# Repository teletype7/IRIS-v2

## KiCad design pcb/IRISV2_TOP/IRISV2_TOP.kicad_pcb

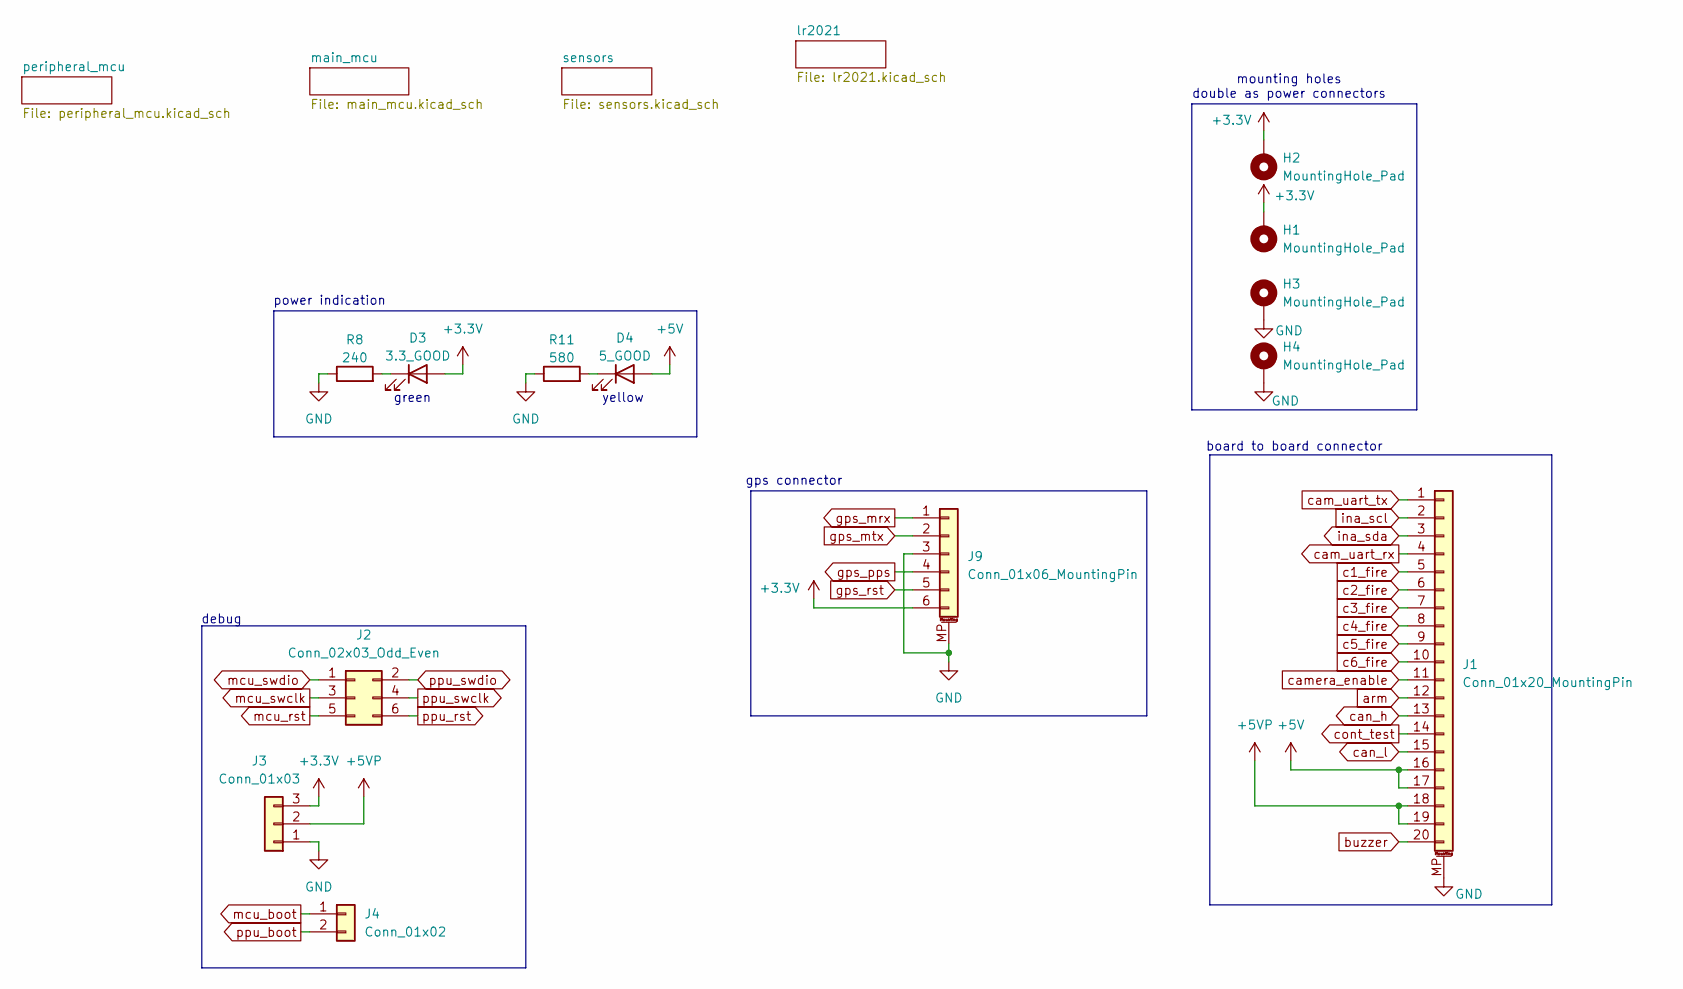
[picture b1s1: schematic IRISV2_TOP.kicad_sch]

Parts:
D3: 3.3_GOOD; LED_0805_2012Metric
D4: 5_GOOD; LED_0805_2012Metric
H1, H2, H3, H4: MountingHole_Pad; MountingHole_3.2mm_M3_ISO7380_Pad_TopBottom
J1: Conn_01x20_MountingPin; FFC3B07-20-T
J2: Conn_02x03_Odd_Even; PinHeader_2x03_P2.54mm_Vertical
J3: Conn_01x03; PinHeader_1x03_P2.54mm_Vertical
J4: Conn_01x02; PinHeader_1x02_P2.54mm_Vertical
J9: Conn_01x06_MountingPin; JST_PH_S6B-PH-SM4-TB_1x06-1MP_P2.00mm_Horizontal
R8: 240; R_0603_1608Metric
R11: 580; R_0603_1608Metric

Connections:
+3.3V: D3.2 (A), H1.1, H2.1, J3.3, J9.6; also elsewhere on the board
+5V: D4.2 (A), J1.16, J1.17; also elsewhere on the board
+5VP: J1.18, J1.19, J3.2
GND: H3.1, H4.1, J1.MP (MountPin), J3.1, J9.3, J9.MP (MountPin), R8.1, R11.1; also elsewhere on the board
unnamed: D3.1 (K), R8.2
unnamed: D4.1 (K), R11.2
arm: J1.12; also elsewhere on the board
buzzer: J1.20; also elsewhere on the board
c1_fire: J1.5; also elsewhere on the board
c2_fire: J1.6; also elsewhere on the board
c3_fire: J1.7; also elsewhere on the board
c4_fire: J1.8; also elsewhere on the board
c5_fire: J1.9; also elsewhere on the board
c6_fire: J1.10; also elsewhere on the board
cam_uart_rx: J1.4; also elsewhere on the board
cam_uart_tx: J1.1; also elsewhere on the board
camera_enable: J1.11; also elsewhere on the board
can_h: J1.13; also elsewhere on the board
can_l: J1.15; also elsewhere on the board
cont_test: J1.14; also elsewhere on the board
gps_mrx: J9.1; also elsewhere on the board
gps_mtx: J9.2; also elsewhere on the board
gps_pps: J9.4
gps_rst: J9.5
ina_scl: J1.2; also elsewhere on the board
ina_sda: J1.3; also elsewhere on the board
mcu_boot: J4.1; also elsewhere on the board
mcu_rst: J2.5; also elsewhere on the board
mcu_swclk: J2.3; also elsewhere on the board
mcu_swdio: J2.1; also elsewhere on the board
ppu_boot: J4.2; also elsewhere on the board
ppu_rst: J2.6; also elsewhere on the board
ppu_swclk: J2.4; also elsewhere on the board
ppu_swdio: J2.2; also elsewhere on the board

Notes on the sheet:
gps connector
debug
board to board connector
power indication
yellow
mounting holes double as power connectors
green

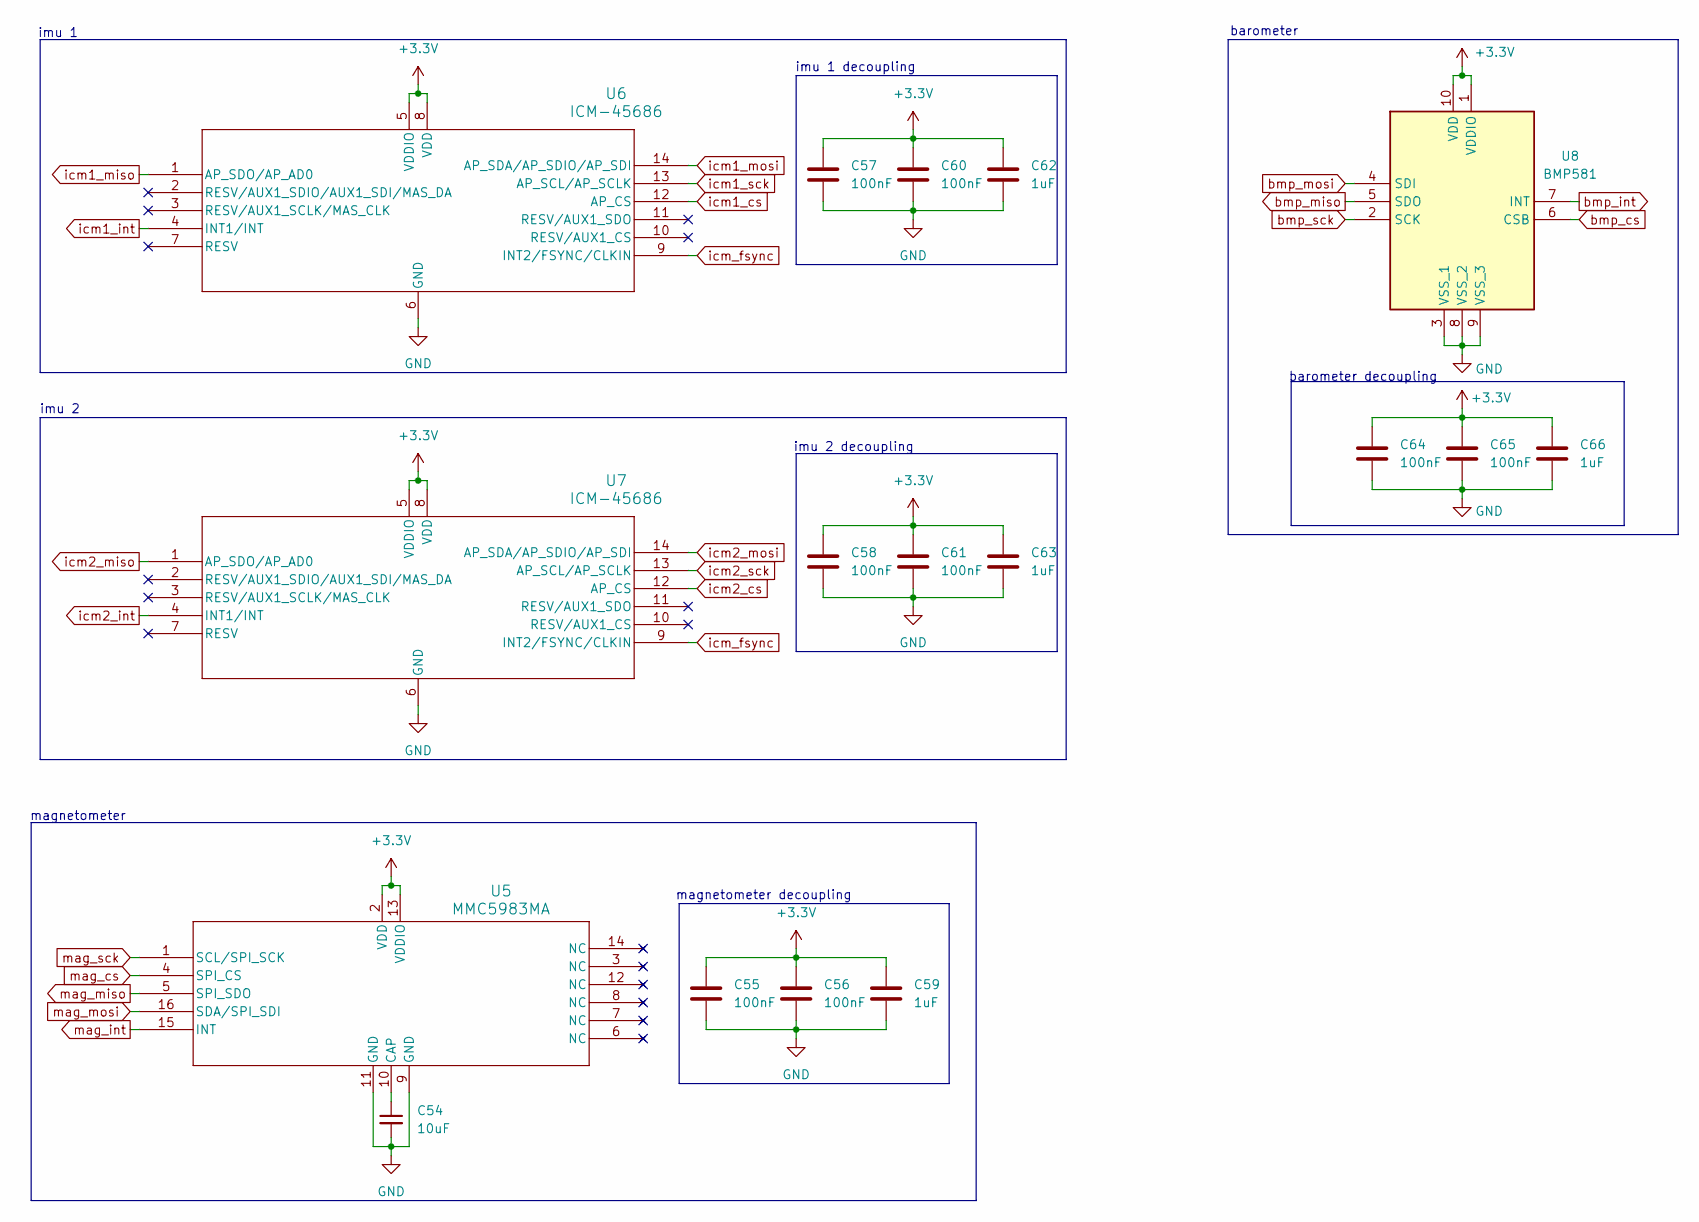
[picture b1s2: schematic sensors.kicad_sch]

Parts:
C54: 10uF; C_0603_1608Metric
C55, C56, C57, C58, C60, C61, C64, C65: 100nF; C_0402_1005Metric
C59, C62, C63, C66: 1uF; C_0603_1608Metric
U5: MMC5983MA; MMC5983MA_MEM
U6, U7: ICM-45686; U_2p5X3X0p81_LGA14L_TDK
U8: BMP581; Mouser Part Number 262-BMP581

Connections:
+3.3V: C55.1, C56.1, C57.1, C58.1, C59.1, C60.1, C61.1, C62.1, C63.1, C64.1, C65.1, C66.1, U5.2 (VDD), U5.13 (VDDIO), U6.5 (VDDIO), U6.8 (VDD), U7.5 (VDDIO), U7.8 (VDD), U8.1 (VDDIO), U8.10 (VDD); also elsewhere on the board
GND: C54.2, C55.2, C56.2, C57.2, C58.2, C59.2, C60.2, C61.2, C62.2, C63.2, C64.2, C65.2, C66.2, U5.9 (GND), U5.11 (GND), U6.6 (GND), U7.6 (GND), U8.3 (VSS_1), U8.8 (VSS_2), U8.9 (VSS_3); also elsewhere on the board
unnamed: C54.1, U5.10 (CAP)
bmp_cs: U8.6 (CSB); also elsewhere on the board
bmp_int: U8.7 (INT); also elsewhere on the board
bmp_miso: U8.5 (SDO); also elsewhere on the board
bmp_mosi: U8.4 (SDI); also elsewhere on the board
bmp_sck: U8.2 (SCK); also elsewhere on the board
icm1_cs: U6.12 (AP_CS); also elsewhere on the board
icm1_int: U6.4 (INT1/INT); also elsewhere on the board
icm1_miso: U6.1 (AP_SDO/AP_AD0); also elsewhere on the board
icm1_mosi: U6.14 (AP_SDA/AP_SDIO/AP_SDI); also elsewhere on the board
icm1_sck: U6.13 (AP_SCL/AP_SCLK); also elsewhere on the board
icm2_cs: U7.12 (AP_CS); also elsewhere on the board
icm2_int: U7.4 (INT1/INT); also elsewhere on the board
icm2_miso: U7.1 (AP_SDO/AP_AD0); also elsewhere on the board
icm2_mosi: U7.14 (AP_SDA/AP_SDIO/AP_SDI); also elsewhere on the board
icm2_sck: U7.13 (AP_SCL/AP_SCLK); also elsewhere on the board
icm_fsync: U6.9 (INT2/FSYNC/CLKIN), U7.9 (INT2/FSYNC/CLKIN); also elsewhere on the board
mag_cs: U5.4 (SPI_CS); also elsewhere on the board
mag_int: U5.15 (INT); also elsewhere on the board
mag_miso: U5.5 (SPI_SDO); also elsewhere on the board
mag_mosi: U5.16 (SDA/SPI_SDI); also elsewhere on the board
mag_sck: U5.1 (SCL/SPI_SCK); also elsewhere on the board

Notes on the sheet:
barometer decoupling
imu 1 decoupling
imu 2 decoupling
imu 1
imu 2
magnetometer decoupling
magnetometer
barometer

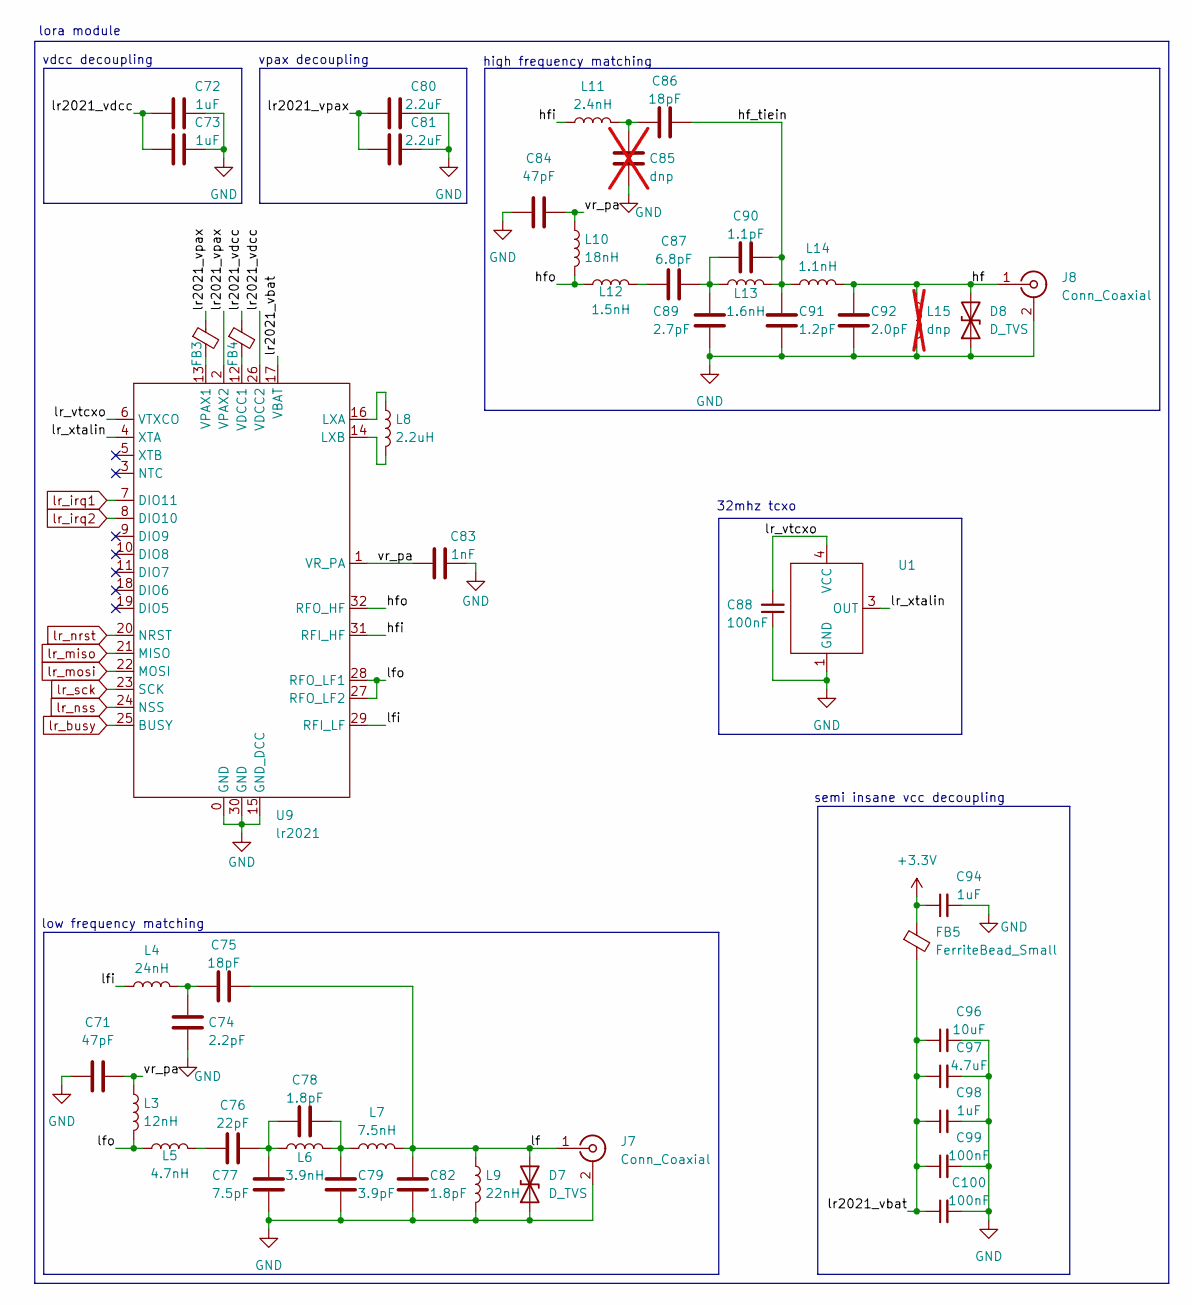
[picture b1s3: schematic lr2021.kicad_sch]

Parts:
C71, C84: 47pF; C_0201_0603Metric
C72, C73, C94, C98: 1uF; C_0603_1608Metric
C74: 2.2pF; C_0201_0603Metric
C75, C86: 18pF; C_0201_0603Metric
C76: 22pF; C_0201_0603Metric
C77: 7.5pF; C_0201_0603Metric
C78, C82: 1.8pF; C_0201_0603Metric
C79: 3.9pF; C_0201_0603Metric
C80, C81: 2.2uF; C_0603_1608Metric
C83: 1nF; C_0402_1005Metric
C85: dnp; C_0201_0603Metric; not fitted
C87: 6.8pF; C_0201_0603Metric
C88, C99, C100: 100nF; C_0402_1005Metric
C89: 2.7pF; C_0201_0603Metric
C90: 1.1pF; C_0201_0603Metric
C91: 1.2pF; C_0201_0603Metric
C92: 2.0pF; C_0201_0603Metric
C96: 10uF; C_0603_1608Metric
C97: 4.7uF; C_0603_1608Metric
D7, D8: D_TVS; D_0201_0603Metric
FB3, FB4, FB5: FerriteBead_Small; L_0402_1005Metric
J7, J8: Conn_Coaxial; U.FL_Hirose_U.FL-R-SMT-1_Vertical
L3: 12nH; L_0402_1005Metric
L4: 24nH; L_0201_0603Metric
L5: 4.7nH; L_0201_0603Metric
L6: 3.9nH; L_0201_0603Metric
L7: 7.5nH; L_0201_0603Metric
L8: 2.2uH; L_0603_1608Metric
L9: 22nH; L_0201_0603Metric
L10: 18nH; L_0201_0603Metric
L11: 2.4nH; L_0201_0603Metric
L12: 1.5nH; L_0201_0603Metric
L13: 1.6nH; L_0201_0603Metric
L14: 1.1nH; L_0201_0603Metric
L15: dnp; L_0201_0603Metric; not fitted
U1: ECS-TXO-20CSMV4
U9: lr2021; LR2021_thermalvias

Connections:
+3.3V: C94.1, FB5.1; also elsewhere on the board
/lr2021/hf: C92.1, D8.2 (A2), J8.1 (In), L14.2, L15.1
/lr2021/hf_tiein: C86.2, C90.2, C91.1, L13.2, L14.1
/lr2021/hfi: L11.1, U9.31 (RFI_HF)
/lr2021/hfo: L10.2, L12.1, U9.32 (RFO_HF)
/lr2021/lf: C75.2, C82.1, D7.2 (A2), J7.1 (In), L7.2, L9.1
/lr2021/lfi: L4.1, U9.29 (RFI_LF)
/lr2021/lfo: L3.2, L5.1, U9.27 (RFO_LF2), U9.28 (RFO_LF1)
/lr2021/lr2021_vbat: C96.1, C97.1, C98.1, C99.1, C100.1, FB5.2, U9.17 (VBAT)
/lr2021/lr2021_vdcc: C72.1, C73.1, FB4.1, U9.26 (VDCC2)
/lr2021/lr2021_vpax: C80.1, C81.1, FB3.1, U9.2 (VPAX2)
/lr2021/lr_vtcxo: C88.2, U1.4 (VCC), U9.6 (VTXCO)
/lr2021/lr_xtalin: U1.3 (OUT), U9.4 (XTA)
/lr2021/vr_pa: C71.2, C83.1, C84.2, L3.1, L10.1, U9.1 (VR_PA)
GND: C71.1, C72.2, C73.2, C74.2, C77.2, C79.2, C80.2, C81.2, C82.2, C83.2, C84.1, C85.2, C88.1, C89.2, C91.2, C92.2, C94.2, C96.2, C97.2, C98.2, C99.2, C100.2, D7.1 (A1), D8.1 (A1), J7.2 (Ext), J8.2 (Ext), L9.2, L15.2, U1.1 (GND), U9.0 (GND), U9.15 (GND_DCC), U9.30 (GND); also elsewhere on the board
unnamed: C74.1, C75.1, L4.2
unnamed: C76.1, L5.2
unnamed: C76.2, C77.1, C78.1, L6.1
unnamed: C78.2, C79.1, L6.2, L7.1
unnamed: C85.1, C86.1, L11.2
unnamed: C87.1, L12.2
unnamed: C87.2, C89.1, C90.1, L13.1
unnamed: L8.1, U9.16 (LXA)
unnamed: L8.2, U9.14 (LXB)
unnamed: FB4.2, U9.12 (VDCC1)
unnamed: FB3.2, U9.13 (VPAX1)
lr_busy: U9.25 (BUSY); also elsewhere on the board
lr_irq1: U9.7 (DIO11); also elsewhere on the board
lr_irq2: U9.8 (DIO10); also elsewhere on the board
lr_miso: U9.21 (MISO); also elsewhere on the board
lr_mosi: U9.22 (MOSI); also elsewhere on the board
lr_nrst: U9.20 (NRST); also elsewhere on the board
lr_nss: U9.24 (NSS); also elsewhere on the board
lr_sck: U9.23 (SCK); also elsewhere on the board

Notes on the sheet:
high frequency matching
lora module
low frequency matching
vdcc decoupling
vpax decoupling
semi insane vcc decoupling
32mhz tcxo

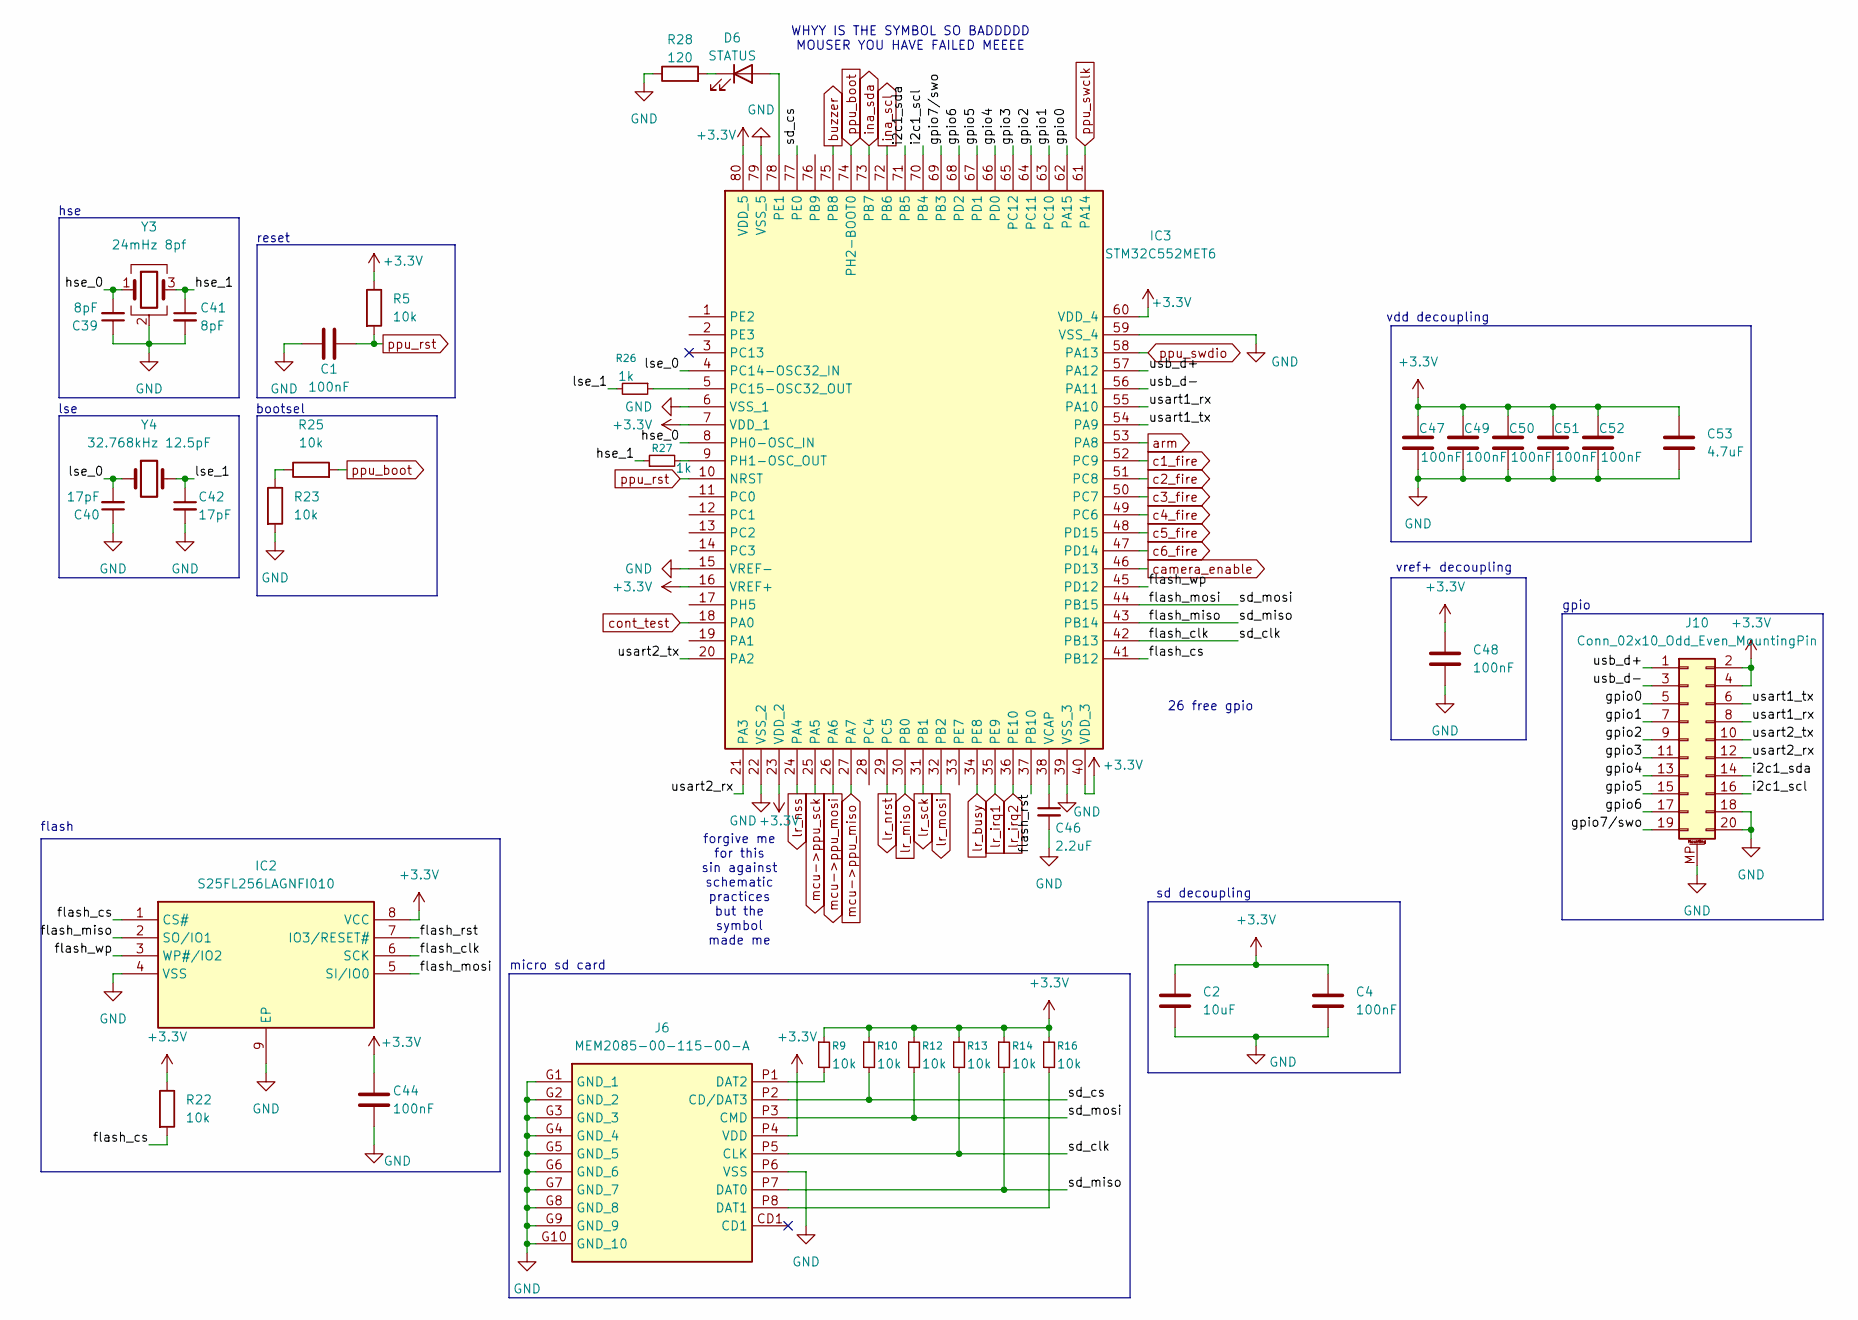
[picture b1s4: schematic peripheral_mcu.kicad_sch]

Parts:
C1, C4, C44, C47, C48, C49, C50, C51, C52: 100nF; C_0402_1005Metric
C2: 10uF; C_0603_1608Metric
C39, C41: 8pF; C_0402_1005Metric
C40, C42: 17pF; C_0402_1005Metric
C46: 2.2uF; C_0603_1608Metric
C53: 4.7uF; C_0603_1608Metric
D6: STATUS; LED_0805_2012Metric
IC2: S25FL256LAGNFI010; SON127P800X600X80-9N-D; Mouser Part Number 727-S25FL256LAGNFI00
IC3: STM32C552MET6; QFP50P1400X1400X160-80N; Manufacturer_Part_Number STM32C552MET6
J6: MEM2085-00-115-00-A; MEM20850011500A; Mouser Part Number 640-MEM20850011500A
J10: Conn_02x10_Odd_Even_MountingPin; AMPHENOL_10164228-0201A1RLF
R5, R9, R10, R12, R13, R14, R16, R22, R23, R25: 10k; R_0402_1005Metric
R26, R27: 1k; R_0402_1005Metric
R28: 120; R_0603_1608Metric
Y3: 24mHz 8pf; Crystal_SMD_3225-4Pin_3.2x2.5mm
Y4: 32.768kHz 12.5pF; Crystal_SMD_3215-2Pin_3.2x1.5mm

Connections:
+3.3V: C2.1, C4.1, C44.1, C47.1, C48.1, C49.1, C50.1, C51.1, C52.1, C53.1, IC2.8 (VCC), IC3.7 (VDD_1), IC3.16 (VREF+), IC3.23 (VDD_2), IC3.40 (VDD_3), IC3.60 (VDD_4), IC3.80 (VDD_5), J6.P4 (VDD), J10.2, J10.4, R5.1, R9.1, R10.1, R12.1, R13.1, R14.1, R16.1, R22.1; also elsewhere on the board
/peripheral_mcu/flash_clk: IC2.6 (SCK), IC3.42 (PB13), J6.P5 (CLK), R13.2
/peripheral_mcu/flash_cs: IC2.1 (CS#), IC3.41 (PB12), R22.2
/peripheral_mcu/flash_miso: IC2.2 (SO/IO1), IC3.43 (PB14), J6.P7 (DAT0), R14.2
/peripheral_mcu/flash_mosi: IC2.5 (SI/IO0), IC3.44 (PB15), J6.P3 (CMD), R12.2
/peripheral_mcu/flash_rst: IC2.7 (IO3/RESET#), IC3.37 (PB10)
/peripheral_mcu/flash_wp: IC2.3 (WP#/IO2), IC3.45 (PD12)
/peripheral_mcu/gpio0: IC3.62 (PA15), J10.5
/peripheral_mcu/gpio1: IC3.63 (PC10), J10.7
/peripheral_mcu/gpio2: IC3.64 (PC11), J10.9
/peripheral_mcu/gpio3: IC3.65 (PC12), J10.11
/peripheral_mcu/gpio4: IC3.66 (PD0), J10.13
/peripheral_mcu/gpio5: IC3.67 (PD1), J10.15
/peripheral_mcu/gpio6: IC3.68 (PD2), J10.17
/peripheral_mcu/gpio7/swo: IC3.69 (PB3), J10.19
/peripheral_mcu/hse_0: C39.2, IC3.8 (PH0-OSC_IN), Y3.1
/peripheral_mcu/hse_1: C41.1, R27.1, Y3.3
/peripheral_mcu/i2c1_scl: IC3.70 (PB4), J10.16
/peripheral_mcu/i2c1_sda: IC3.71 (PB5), J10.14
/peripheral_mcu/lse_0: C40.2, IC3.4 (PC14-OSC32_IN), Y4.1
/peripheral_mcu/lse_1: C42.1, R26.2, Y4.2
/peripheral_mcu/sd_cs: IC3.77 (PE0), J6.P2 (CD/DAT3), R10.2
/peripheral_mcu/usart1_rx: IC3.55 (PA10), J10.8
/peripheral_mcu/usart1_tx: IC3.54 (PA9), J10.6
/peripheral_mcu/usart2_rx: IC3.21 (PA3), J10.12
/peripheral_mcu/usart2_tx: IC3.20 (PA2), J10.10
/peripheral_mcu/usb_d+: IC3.57 (PA12), J10.1
/peripheral_mcu/usb_d-: IC3.56 (PA11), J10.3
GND: C1.2, C2.2, C4.2, C39.1, C40.1, C41.2, C42.2, C44.2, C46.2, C47.2, C48.2, C49.2, C50.2, C51.2, C52.2, C53.2, IC2.4 (VSS), IC2.9 (EP), IC3.6 (VSS_1), IC3.15 (VREF-), IC3.22 (VSS_2), IC3.39 (VSS_3), IC3.59 (VSS_4), IC3.79 (VSS_5), J6.G1 (GND_1), J6.G2 (GND_2), J6.G3 (GND_3), J6.G4 (GND_4), J6.G5 (GND_5), J6.G6 (GND_6), J6.G7 (GND_7), J6.G8 (GND_8), J6.G9 (GND_9), J6.G10 (GND_10), J6.P6 (VSS), J10.18, J10.20, J10.MP (MountPin), R23.2, R28.1, Y3.2 (G), Y3.4 (G); also elsewhere on the board
unnamed: D6.2 (A), IC3.78 (PE1)
unnamed: D6.1 (K), R28.2
unnamed: IC3.5 (PC15-OSC32_OUT), R26.1
unnamed: IC3.9 (PH1-OSC_OUT), R27.2
unnamed: C46.1, IC3.38 (VCAP)
unnamed: J6.P8 (DAT1), R16.2
unnamed: J6.P1 (DAT2), R9.2
unnamed: R23.1, R25.1
arm: IC3.53 (PA8); also elsewhere on the board
buzzer: IC3.75 (PB8); also elsewhere on the board
c1_fire: IC3.52 (PC9); also elsewhere on the board
c2_fire: IC3.51 (PC8); also elsewhere on the board
c3_fire: IC3.50 (PC7); also elsewhere on the board
c4_fire: IC3.49 (PC6); also elsewhere on the board
c5_fire: IC3.48 (PD15); also elsewhere on the board
c6_fire: IC3.47 (PD14); also elsewhere on the board
camera_enable: IC3.46 (PD13); also elsewhere on the board
cont_test: IC3.18 (PA0); also elsewhere on the board
ina_scl: IC3.72 (PB6); also elsewhere on the board
ina_sda: IC3.73 (PB7); also elsewhere on the board
lr_busy: IC3.34 (PE8); also elsewhere on the board
lr_irq1: IC3.35 (PE9); also elsewhere on the board
lr_irq2: IC3.36 (PE10); also elsewhere on the board
lr_miso: IC3.30 (PB0); also elsewhere on the board
lr_mosi: IC3.32 (PB2); also elsewhere on the board
lr_nrst: IC3.29 (PC5); also elsewhere on the board
lr_nss: IC3.24 (PA4); also elsewhere on the board
lr_sck: IC3.31 (PB1); also elsewhere on the board
mcu->ppu_miso: IC3.27 (PA7); also elsewhere on the board
mcu->ppu_mosi: IC3.26 (PA6); also elsewhere on the board
mcu->ppu_sck: IC3.25 (PA5); also elsewhere on the board
ppu_boot: IC3.74 (PH2-BOOT0), R25.2; also elsewhere on the board
ppu_rst: C1.1, IC3.10 (NRST), R5.2; also elsewhere on the board
ppu_swclk: IC3.61 (PA14); also elsewhere on the board
ppu_swdio: IC3.58 (PA13); also elsewhere on the board

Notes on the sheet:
forgive me for this sin against schematic practices but the symbol made me
micro sd card
vref+ decoupling
gpio
lse
flash
sd decoupling
26 free gpio
vdd decoupling
reset
hse
bootsel
WHYY IS THE SYMBOL SO BADDDDD MOUSER YOU HAVE FAILED MEEEE

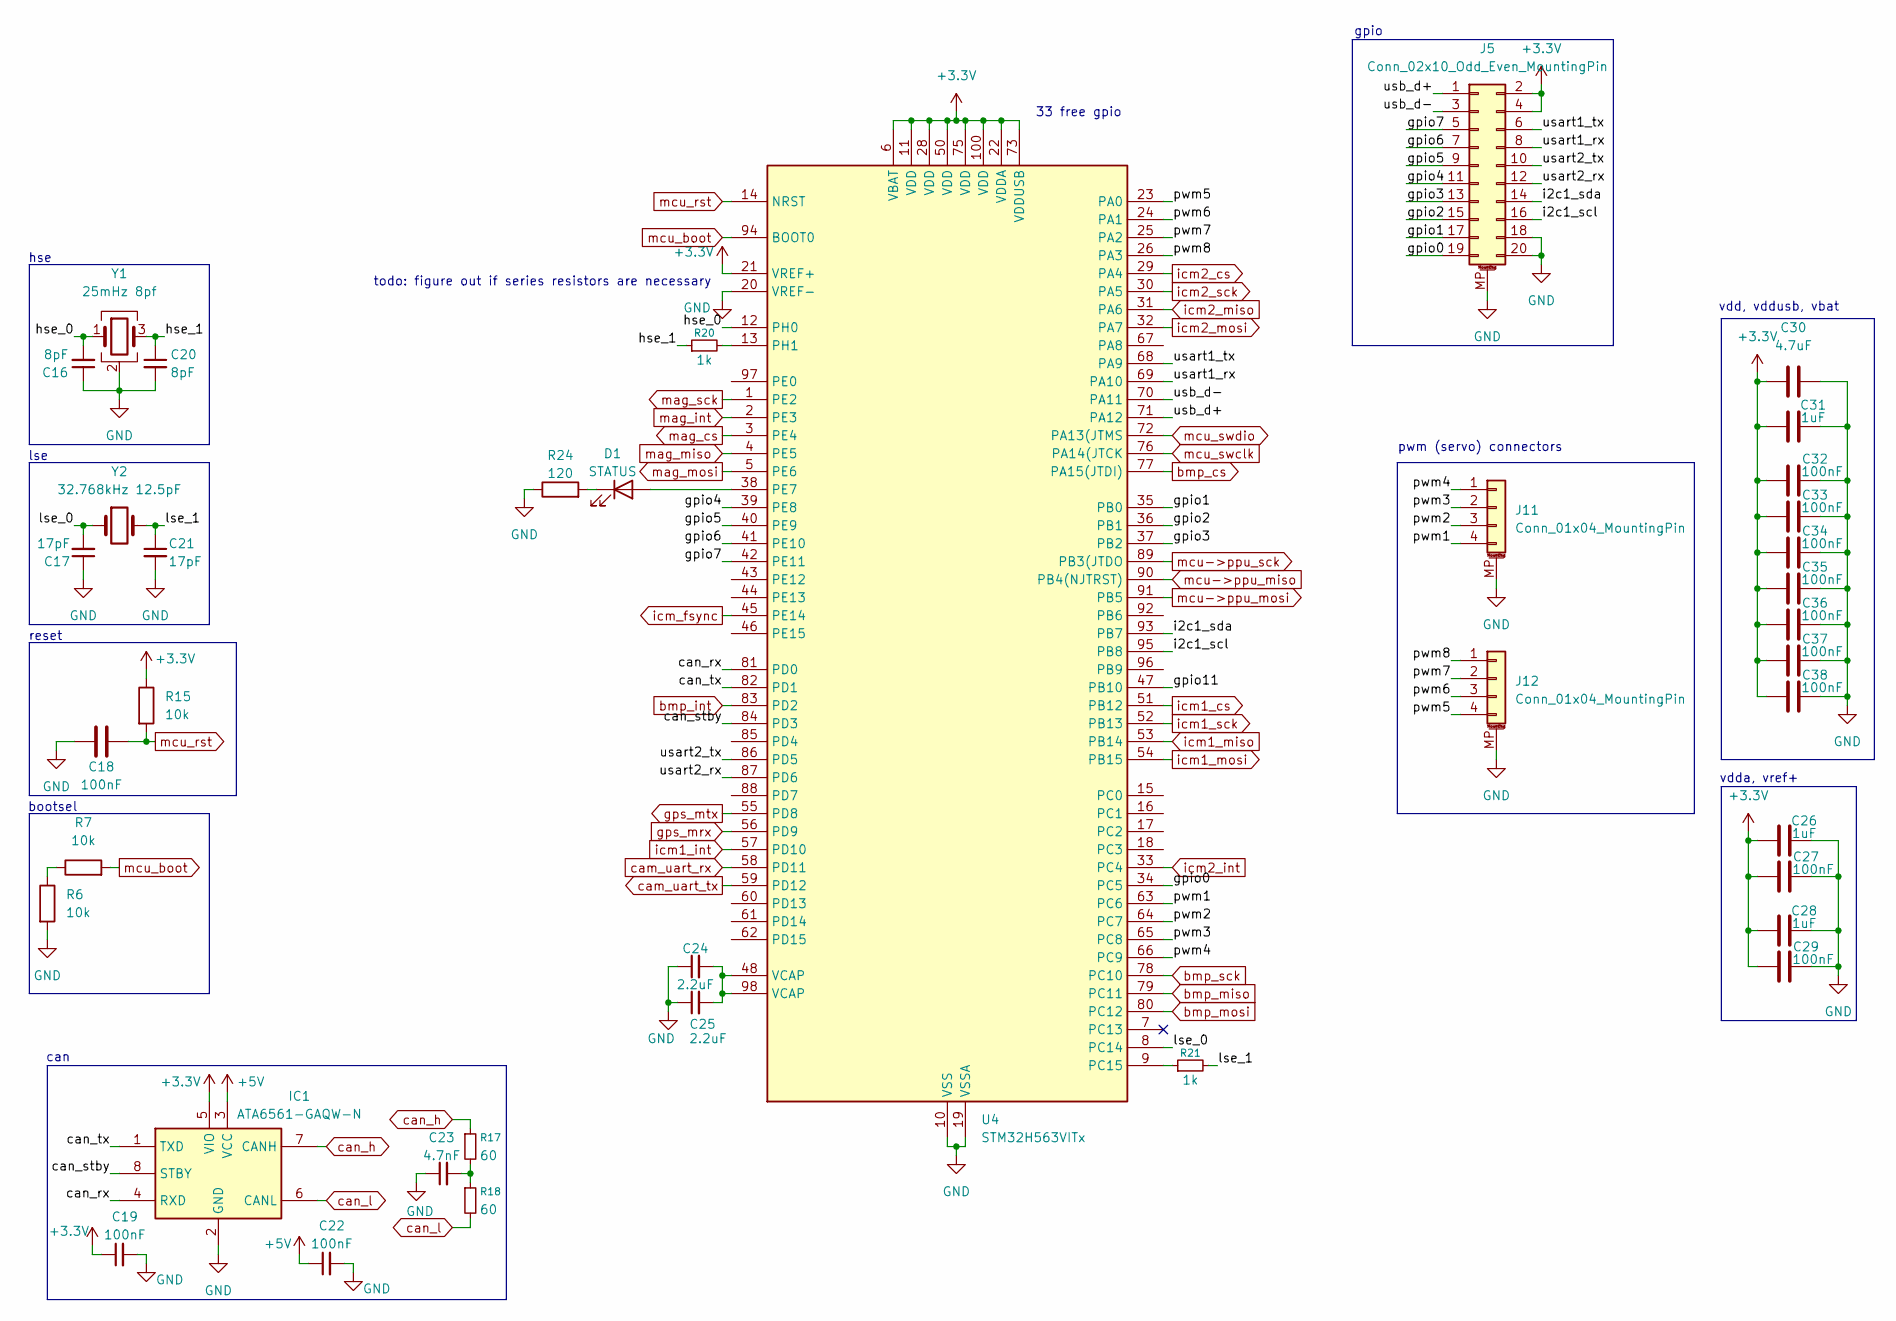
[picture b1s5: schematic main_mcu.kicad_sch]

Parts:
C16, C20: 8pF; C_0402_1005Metric
C17, C21: 17pF; C_0402_1005Metric
C18, C19, C22, C27, C29, C32, C33, C34, C35, C36, C37, C38: 100nF; C_0402_1005Metric
C23: 4.7nF; C_0402_1005Metric
C24, C25: 2.2uF; C_0603_1608Metric
C26, C28, C31: 1uF; C_0603_1608Metric
C30: 4.7uF; C_0603_1608Metric
D1: STATUS; LED_0805_2012Metric
IC1: ATA6561-GAQW-N; SOIC127P600X175-8N; Mouser Part Number 579-ATA6561-GAQW-N
J5: Conn_02x10_Odd_Even_MountingPin; AMPHENOL_10164228-0201A1RLF
J11, J12: Conn_01x04_MountingPin; JST_PH_S4B-PH-SM4-TB_1x04-1MP_P2.00mm_Horizontal
R6, R7, R15: 10k; R_0402_1005Metric
R17, R18: 60; R_0402_1005Metric
R20, R21: 1k; R_0402_1005Metric
R24: 120; R_0603_1608Metric
U4: STM32H563VITx; LQFP-100_14x14mm_P0.5mm
Y1: 25mHz 8pf; Crystal_SMD_3225-4Pin_3.2x2.5mm
Y2: 32.768kHz 12.5pF; Crystal_SMD_3215-2Pin_3.2x1.5mm

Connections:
+3.3V: C19.1, C26.1, C27.1, C28.1, C29.1, C30.1, C31.1, C32.1, C33.1, C34.1, C35.1, C36.1, C37.1, C38.1, IC1.5 (VIO), J5.2, J5.4, R15.1, U4.6 (VBAT), U4.11 (VDD), U4.21 (VREF+), U4.22 (VDDA), U4.28 (VDD), U4.50 (VDD), U4.73 (VDDUSB), U4.75 (VDD), U4.100 (VDD); also elsewhere on the board
+5V: C22.1, IC1.3 (VCC); also elsewhere on the board
/main_mcu/can_rx: IC1.4 (RXD), U4.81 (PD0)
/main_mcu/can_stby: IC1.8 (STBY), U4.84 (PD3)
/main_mcu/can_tx: IC1.1 (TXD), U4.82 (PD1)
/main_mcu/gpio0: J5.19, U4.34 (PC5)
/main_mcu/gpio1: J5.17, U4.35 (PB0)
/main_mcu/gpio2: J5.15, U4.36 (PB1)
/main_mcu/gpio3: J5.13, U4.37 (PB2)
/main_mcu/gpio4: J5.11, U4.39 (PE8)
/main_mcu/gpio5: J5.9, U4.40 (PE9)
/main_mcu/gpio6: J5.7, U4.41 (PE10)
/main_mcu/gpio7: J5.5, U4.42 (PE11)
/main_mcu/gpio11: U4.47 (PB10)
/main_mcu/hse_0: C16.2, U4.12 (PH0), Y1.1
/main_mcu/hse_1: C20.1, R20.1, Y1.3
/main_mcu/i2c1_scl: J5.16, U4.95 (PB8)
/main_mcu/i2c1_sda: J5.14, U4.93 (PB7)
/main_mcu/lse_0: C17.2, U4.8 (PC14), Y2.1
/main_mcu/lse_1: C21.1, R21.2, Y2.2
/main_mcu/pwm1: J11.4, U4.63 (PC6)
/main_mcu/pwm2: J11.3, U4.64 (PC7)
/main_mcu/pwm3: J11.2, U4.65 (PC8)
/main_mcu/pwm4: J11.1, U4.66 (PC9)
/main_mcu/pwm5: J12.4, U4.23 (PA0)
/main_mcu/pwm6: J12.3, U4.24 (PA1)
/main_mcu/pwm7: J12.2, U4.25 (PA2)
/main_mcu/pwm8: J12.1, U4.26 (PA3)
/main_mcu/usart1_rx: J5.8, U4.69 (PA10)
/main_mcu/usart1_tx: J5.6, U4.68 (PA9)
/main_mcu/usart2_rx: J5.12, U4.87 (PD6)
/main_mcu/usart2_tx: J5.10, U4.86 (PD5)
/main_mcu/usb_d+: J5.1, U4.71 (PA12)
/main_mcu/usb_d-: J5.3, U4.70 (PA11)
GND: C16.1, C17.1, C18.2, C19.2, C20.2, C21.2, C22.2, C23.1, C24.1, C25.1, C26.2, C27.2, C28.2, C29.2, C30.2, C31.2, C32.2, C33.2, C34.2, C35.2, C36.2, C37.2, C38.2, IC1.2 (GND), J5.18, J5.20, J5.MP (MountPin), J11.MP (MountPin), J12.MP (MountPin), R6.2, R24.1, U4.10 (VSS), U4.19 (VSSA), U4.20 (VREF-), U4.27 (VSS), U4.49 (VSS), U4.74 (VSS), U4.99 (VSS), Y1.2 (G), Y1.4 (G); also elsewhere on the board
unnamed: C23.2, R17.2, R18.1
unnamed: C24.2, C25.2, U4.48 (VCAP), U4.98 (VCAP)
unnamed: D1.2 (A), U4.38 (PE7)
unnamed: D1.1 (K), R24.2
unnamed: R6.1, R7.1
unnamed: R21.1, U4.9 (PC15)
unnamed: R20.2, U4.13 (PH1)
bmp_cs: U4.77 (PA15(JTDI)); also elsewhere on the board
bmp_int: U4.83 (PD2); also elsewhere on the board
bmp_miso: U4.79 (PC11); also elsewhere on the board
bmp_mosi: U4.80 (PC12); also elsewhere on the board
bmp_sck: U4.78 (PC10); also elsewhere on the board
cam_uart_rx: U4.58 (PD11); also elsewhere on the board
cam_uart_tx: U4.59 (PD12); also elsewhere on the board
can_h: IC1.7 (CANH), R17.1; also elsewhere on the board
can_l: IC1.6 (CANL), R18.2; also elsewhere on the board
gps_mrx: U4.56 (PD9); also elsewhere on the board
gps_mtx: U4.55 (PD8); also elsewhere on the board
icm1_cs: U4.51 (PB12); also elsewhere on the board
icm1_int: U4.57 (PD10); also elsewhere on the board
icm1_miso: U4.53 (PB14); also elsewhere on the board
icm1_mosi: U4.54 (PB15); also elsewhere on the board
icm1_sck: U4.52 (PB13); also elsewhere on the board
icm2_cs: U4.29 (PA4); also elsewhere on the board
icm2_int: U4.33 (PC4); also elsewhere on the board
icm2_miso: U4.31 (PA6); also elsewhere on the board
icm2_mosi: U4.32 (PA7); also elsewhere on the board
icm2_sck: U4.30 (PA5); also elsewhere on the board
icm_fsync: U4.45 (PE14); also elsewhere on the board
mag_cs: U4.3 (PE4); also elsewhere on the board
mag_int: U4.2 (PE3); also elsewhere on the board
mag_miso: U4.4 (PE5); also elsewhere on the board
mag_mosi: U4.5 (PE6); also elsewhere on the board
mag_sck: U4.1 (PE2); also elsewhere on the board
mcu->ppu_miso: U4.90 (PB4(NJTRST)); also elsewhere on the board
mcu->ppu_mosi: U4.91 (PB5); also elsewhere on the board
mcu->ppu_sck: U4.89 (PB3(JTDO); also elsewhere on the board
mcu_boot: R7.2, U4.94 (BOOT0); also elsewhere on the board
mcu_rst: C18.1, R15.2, U4.14 (NRST); also elsewhere on the board
mcu_swclk: U4.76 (PA14(JTCK); also elsewhere on the board
mcu_swdio: U4.72 (PA13(JTMS); also elsewhere on the board

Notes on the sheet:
vdd, vddusb, vbat
lse
todo: figure out if series resistors are necessary
can
reset
bootsel
pwm (servo) connectors
vdda, vref+
33 free gpio
hse
gpio

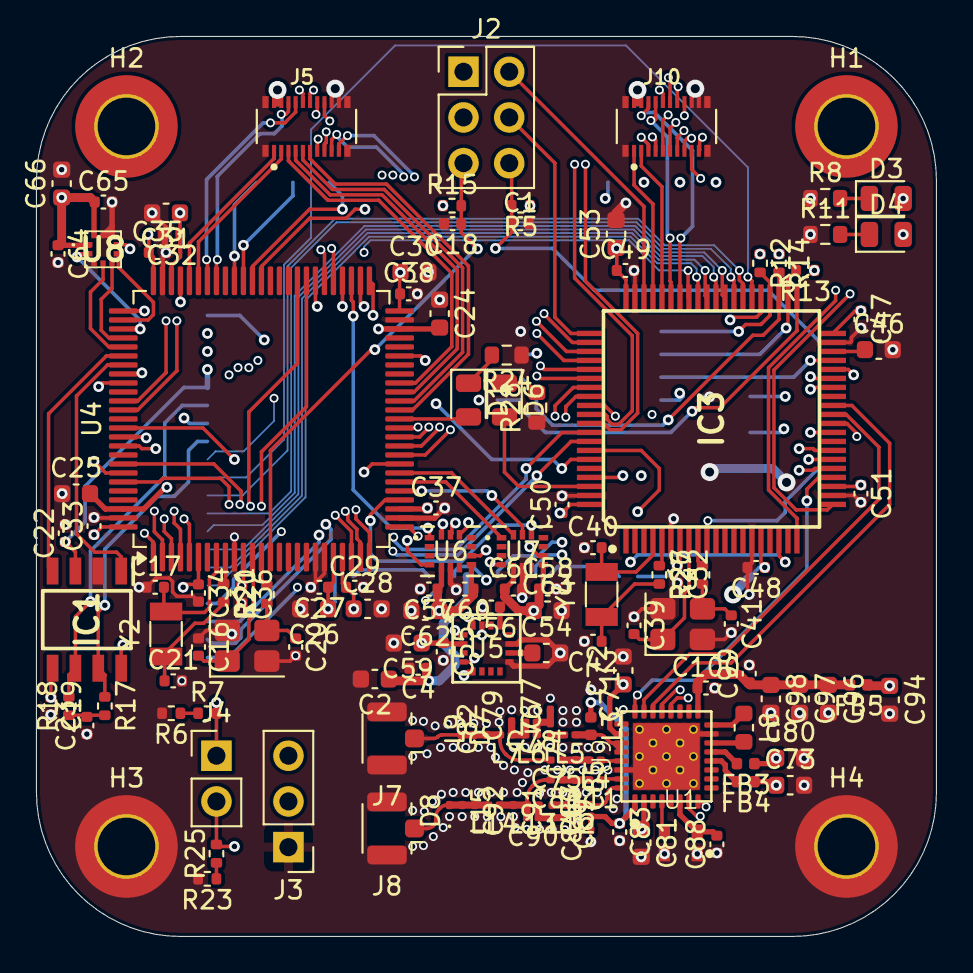
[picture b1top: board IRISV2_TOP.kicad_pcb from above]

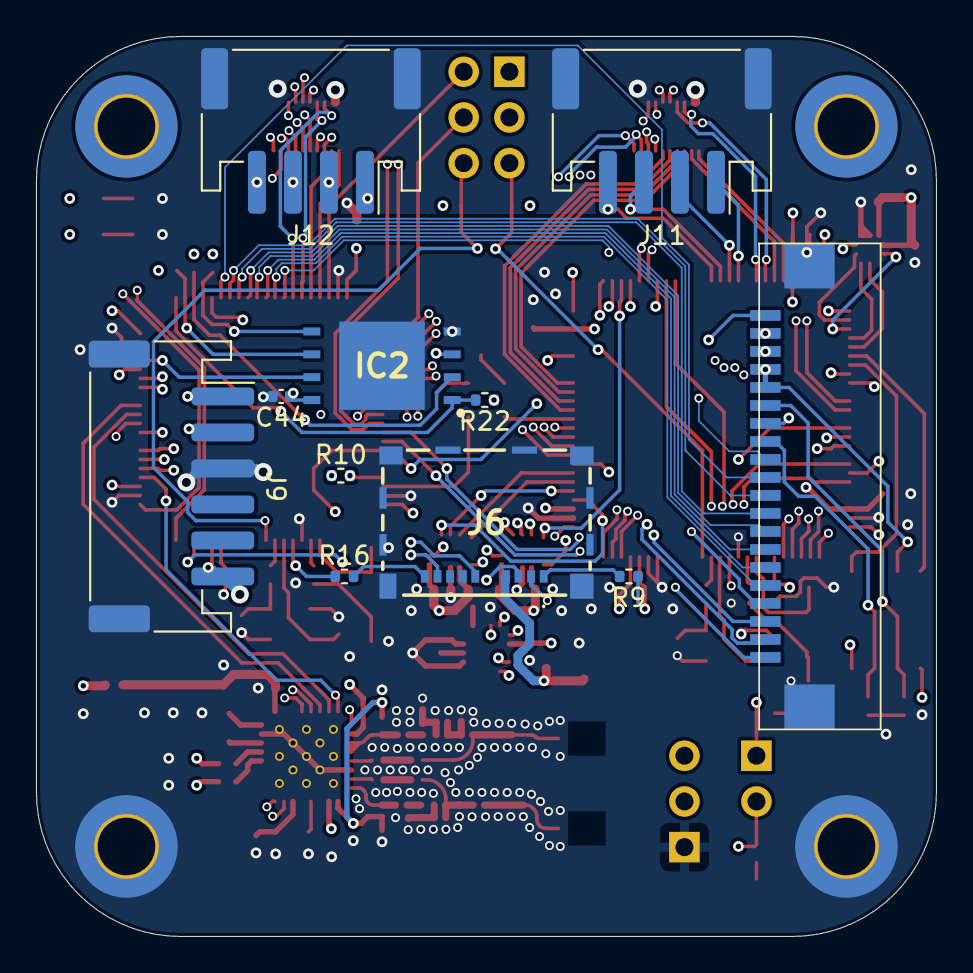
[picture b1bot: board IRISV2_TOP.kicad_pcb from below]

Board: 6 copper layers, 50.0 x 50.0 mm, 155 parts (11 on the bottom side), 162 nets.
